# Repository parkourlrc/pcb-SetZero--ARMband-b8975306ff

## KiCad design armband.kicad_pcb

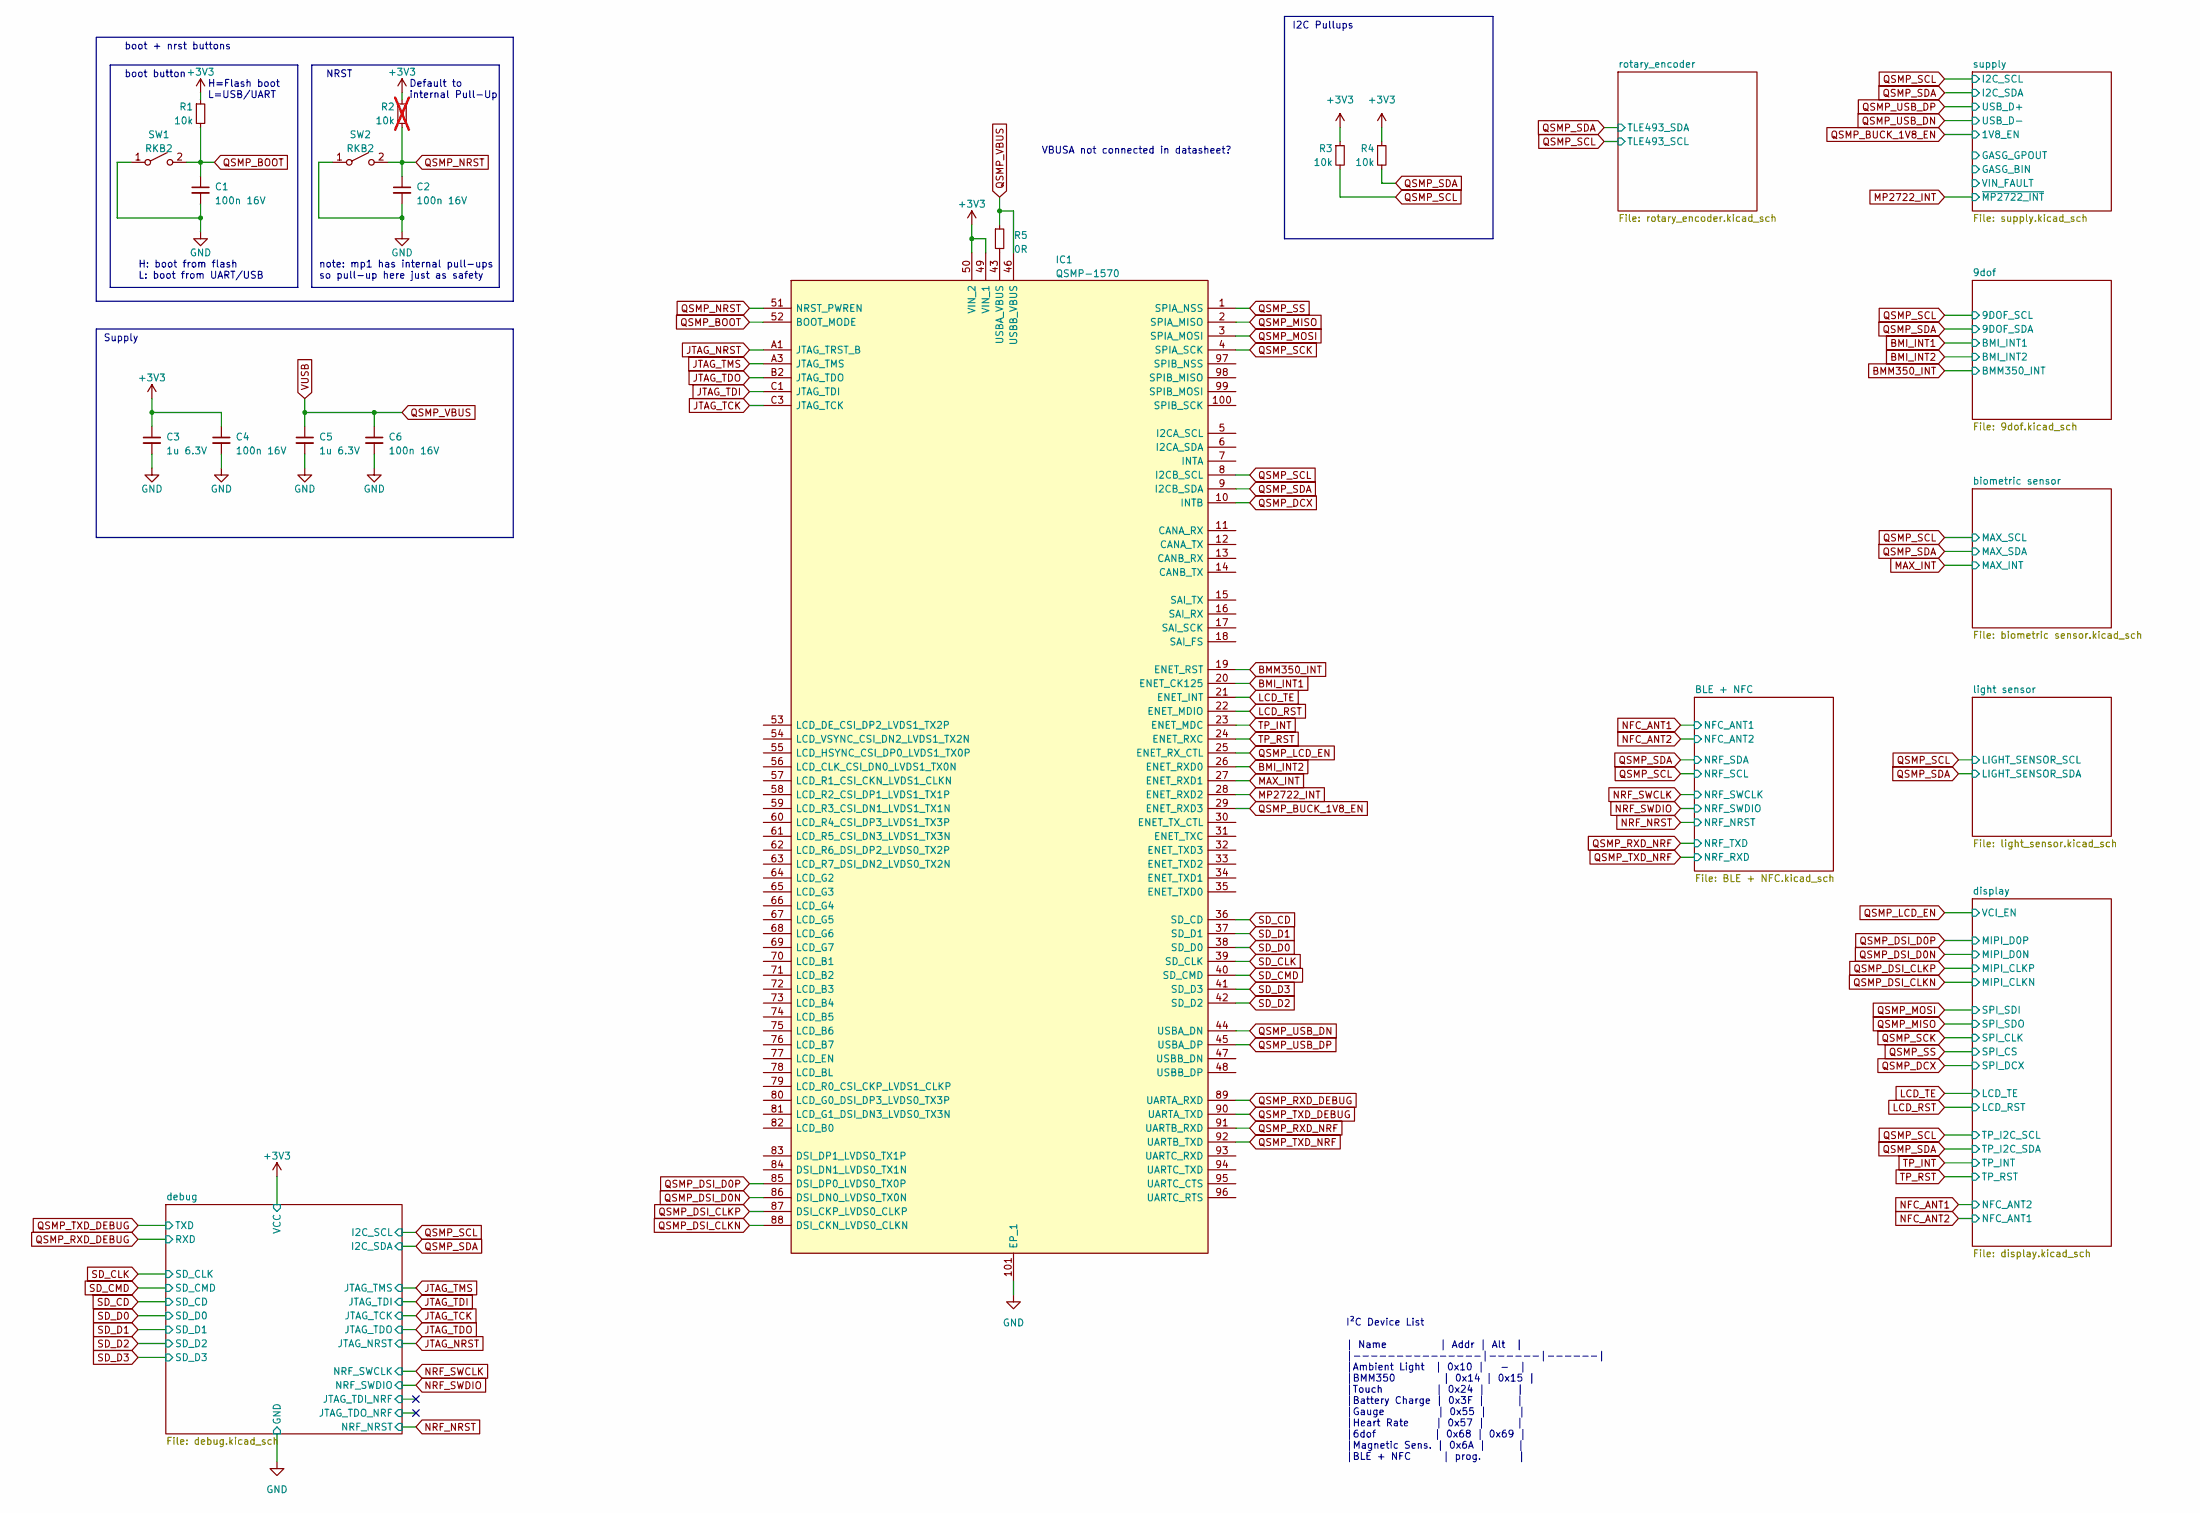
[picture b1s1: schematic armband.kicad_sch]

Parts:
C1, C2, C4, C6: 100n 16V; C_0402_1005Metric
C3, C5: 1u 6.3V; C_0201_0603Metric
IC1: QSMP-1570; QSMP1570_better; Mouser Part Number 951-QSMP-1570
R1: 10k; R_0201_0603Metric
R2: 10k; R_0201_0603Metric; not fitted
R3, R4: 10k; R_0603_1608Metric
R5: 0R; R_0201_0603Metric
SW1, SW2: RKB2

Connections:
+3V3: C3.1, C4.1, IC1.49 (VIN_1), IC1.50 (VIN_2), R1.1, R2.1, R3.1, R4.1; also elsewhere on the board
BMI_INT1: IC1.20 (ENET_CK125); also elsewhere on the board
BMI_INT2: IC1.26 (ENET_RXD0); also elsewhere on the board
BMM350_INT: IC1.19 (ENET_RST); also elsewhere on the board
GND: C1.2, C2.2, C3.2, C4.2, C5.2, C6.2, IC1.101 (EP_1), SW1.1 (A), SW2.1 (A); also elsewhere on the board
JTAG_NRST: IC1.A1 (JTAG_TRST_B); also elsewhere on the board
JTAG_TCK: IC1.C3 (JTAG_TCK); also elsewhere on the board
JTAG_TDI: IC1.C1 (JTAG_TDI); also elsewhere on the board
JTAG_TDO: IC1.B2 (JTAG_TDO); also elsewhere on the board
JTAG_TMS: IC1.A3 (JTAG_TMS); also elsewhere on the board
LCD_RST: IC1.22 (ENET_MDIO); also elsewhere on the board
LCD_TE: IC1.21 (ENET_INT); also elsewhere on the board
MAX_INT: IC1.27 (ENET_RXD1); also elsewhere on the board
MP2722_INT: IC1.28 (ENET_RXD2); also elsewhere on the board
unnamed: IC1.43 (USBA_VBUS), R5.2
QSMP_BOOT: C1.1, IC1.52 (BOOT_MODE), R1.2, SW1.2 (B)
QSMP_BUCK_1V8_EN: IC1.29 (ENET_RXD3); also elsewhere on the board
QSMP_DCX: IC1.10 (INTB); also elsewhere on the board
QSMP_DSI_CLKN: IC1.88 (DSI_CKN_LVDS0_CLKN); also elsewhere on the board
QSMP_DSI_CLKP: IC1.87 (DSI_CKP_LVDS0_CLKP); also elsewhere on the board
QSMP_DSI_D0N: IC1.86 (DSI_DN0_LVDS0_TX0N); also elsewhere on the board
QSMP_DSI_D0P: IC1.85 (DSI_DP0_LVDS0_TX0P); also elsewhere on the board
QSMP_LCD_EN: IC1.25 (ENET_RX_CTL); also elsewhere on the board
QSMP_MISO: IC1.2 (SPIA_MISO); also elsewhere on the board
QSMP_MOSI: IC1.3 (SPIA_MOSI); also elsewhere on the board
QSMP_NRST: C2.1, IC1.51 (NRST_PWREN), R2.2, SW2.2 (B)
QSMP_RXD_DEBUG: IC1.89 (UARTA_RXD); also elsewhere on the board
QSMP_RXD_NRF: IC1.91 (UARTB_RXD); also elsewhere on the board
QSMP_SCK: IC1.4 (SPIA_SCK); also elsewhere on the board
QSMP_SCL: IC1.8 (I2CB_SCL), R3.2; also elsewhere on the board
QSMP_SDA: IC1.9 (I2CB_SDA), R4.2; also elsewhere on the board
QSMP_SS: IC1.1 (SPIA_NSS); also elsewhere on the board
QSMP_TXD_DEBUG: IC1.90 (UARTA_TXD); also elsewhere on the board
QSMP_TXD_NRF: IC1.92 (UARTB_TXD); also elsewhere on the board
QSMP_USB_DN: IC1.44 (USBA_DN); also elsewhere on the board
QSMP_USB_DP: IC1.45 (USBA_DP); also elsewhere on the board
QSMP_VBUS: C5.1, C6.1, IC1.46 (USBB_VBUS), R5.1; also elsewhere on the board
SD_CD: IC1.36 (SD_CD); also elsewhere on the board
SD_CLK: IC1.39 (SD_CLK); also elsewhere on the board
SD_CMD: IC1.40 (SD_CMD); also elsewhere on the board
SD_D0: IC1.38 (SD_D0); also elsewhere on the board
SD_D1: IC1.37 (SD_D1); also elsewhere on the board
SD_D2: IC1.42 (SD_D2); also elsewhere on the board
SD_D3: IC1.41 (SD_D3); also elsewhere on the board
TP_INT: IC1.23 (ENET_MDC); also elsewhere on the board
TP_RST: IC1.24 (ENET_RXC); also elsewhere on the board

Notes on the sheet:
note: mp1 has internal pull-ups so pull-up here just as safety
boot + nrst buttons
NRST
H: boot from flash L: boot from UART/USB
boot button
I²C Device List | Name | Addr | Alt | |---------------|------|------| |Ambient Light | 0x10 | - | |BMM350 | 0x14 | 0x15 | |Touch | 0x24 | | |Battery Charge | 0x3F | | |Gauge | 0x55 | | |Heart Rate | 0x57 | | |6dof | 0x68 | 0x69 | |Magnetic Sens. | 0x6A | | |BLE + NFC | prog. |
VBUSA not connected in datasheet?
I2C Pullups
Default to internal Pull-Up
Supply
H=Flash boot L=USB/UART

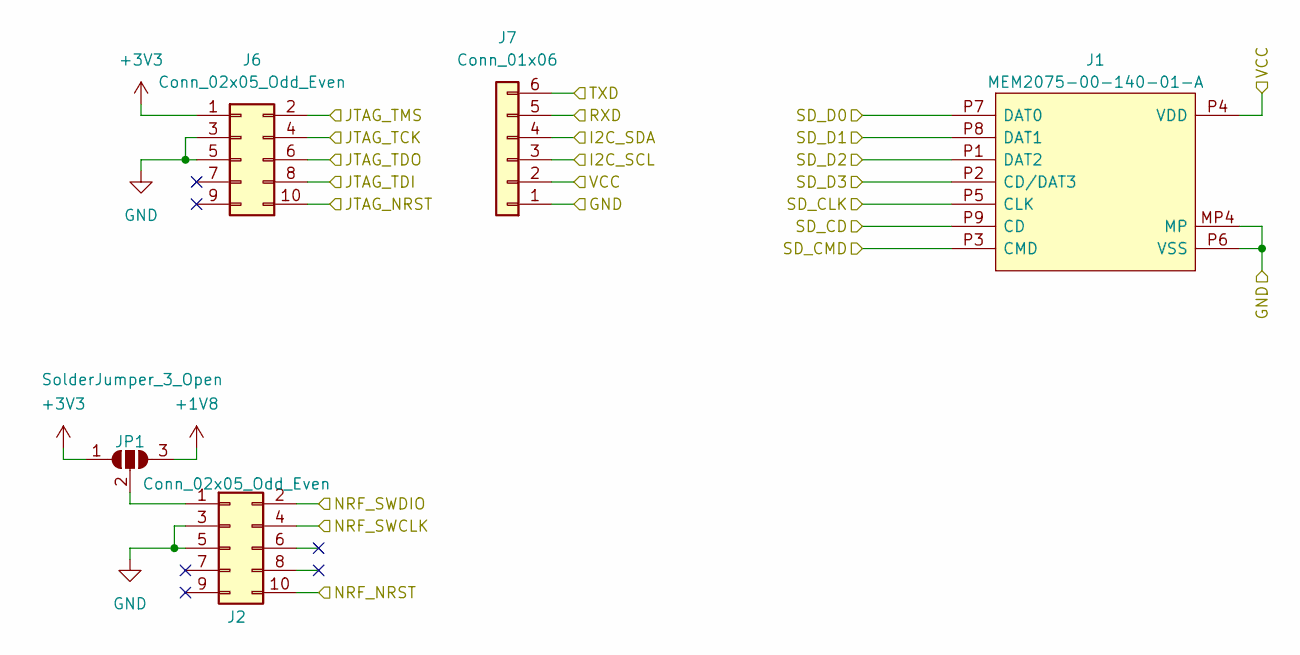
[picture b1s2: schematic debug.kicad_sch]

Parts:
J1: MEM2075-00-140-01-A; MEM20750014001A
J2, J6: Conn_02x05_Odd_Even; 2002112100010T4LF
J7: Conn_01x06; PinHeader_1x06_P2.54mm_Vertical
JP1: SolderJumper_3_Open; SolderJumper-3_P2.0mm_Open_TrianglePad1.0x1.5mm

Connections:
+1V8: JP1.3 (B); also elsewhere on the board
+3V3: J1.P4 (VDD), J6.1, J7.2, JP1.1 (A); also elsewhere on the board
GND: J1.MP1, J1.MP2, J1.MP3, J1.MP4 (MP), J1.P6 (VSS), J2.3, J2.5, J6.3, J6.5, J7.1; also elsewhere on the board
JTAG_NRST: J6.10; also elsewhere on the board
JTAG_TCK: J6.4; also elsewhere on the board
JTAG_TDI: J6.8; also elsewhere on the board
JTAG_TDO: J6.6; also elsewhere on the board
JTAG_TMS: J6.2; also elsewhere on the board
NRF_NRST: J2.10; also elsewhere on the board
NRF_SWCLK: J2.4; also elsewhere on the board
NRF_SWDIO: J2.2; also elsewhere on the board
unnamed: J2.1, JP1.2 (C)
QSMP_RXD_DEBUG: J7.5; also elsewhere on the board
QSMP_SCL: J7.3; also elsewhere on the board
QSMP_SDA: J7.4; also elsewhere on the board
QSMP_TXD_DEBUG: J7.6; also elsewhere on the board
SD_CD: J1.P9 (CD); also elsewhere on the board
SD_CLK: J1.P5 (CLK); also elsewhere on the board
SD_CMD: J1.P3 (CMD); also elsewhere on the board
SD_D0: J1.P7 (DAT0); also elsewhere on the board
SD_D1: J1.P8 (DAT1); also elsewhere on the board
SD_D2: J1.P1 (DAT2); also elsewhere on the board
SD_D3: J1.P2 (CD/DAT3); also elsewhere on the board

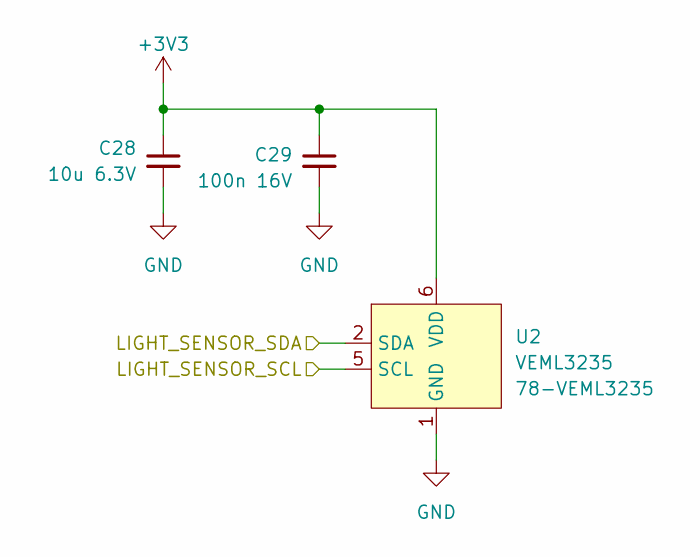
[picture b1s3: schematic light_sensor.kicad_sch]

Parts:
C28: 10u 6.3V; C_0402_1005Metric
C29: 100n 16V; C_0402_1005Metric
U2: VEML3235

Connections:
+3V3: C28.1, C29.1, U2.6 (VDD); also elsewhere on the board
GND: C28.2, C29.2, U2.1 (GND); also elsewhere on the board
QSMP_SCL: U2.5 (SCL); also elsewhere on the board
QSMP_SDA: U2.2 (SDA); also elsewhere on the board

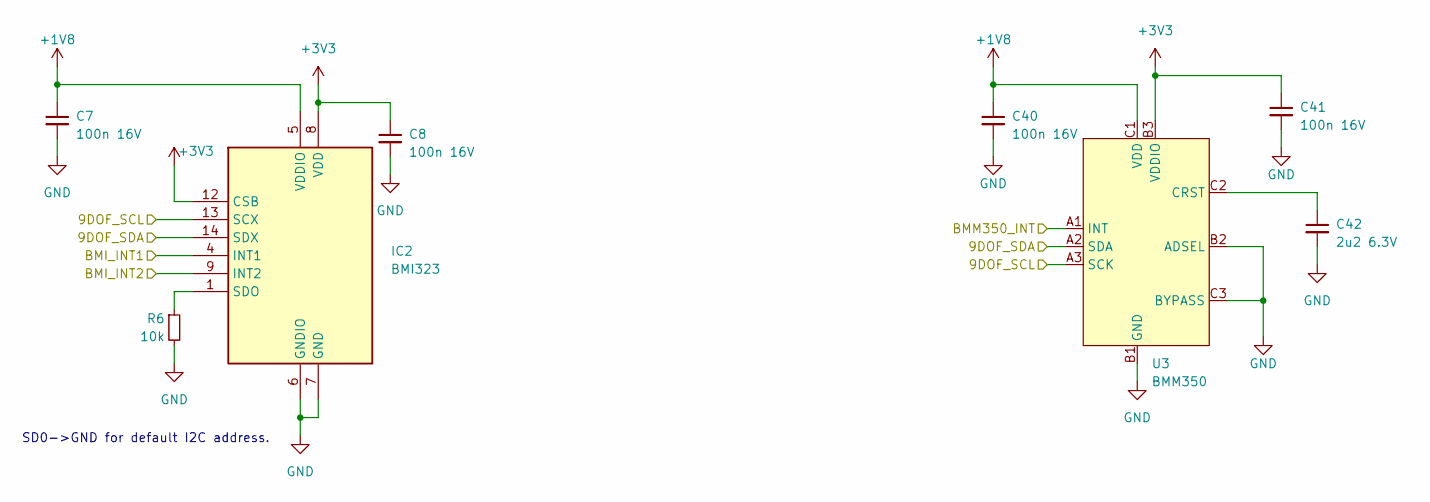
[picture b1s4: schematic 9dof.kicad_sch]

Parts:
C7, C8, C40, C41: 100n 16V; C_0402_1005Metric
C42: 2u2 6.3V; C_0201_0603Metric
IC2: BMI323; Mouser Part Number 262-BMI323
R6: 10k; R_0201_0603Metric
U3: BMM350; bmm350

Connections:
+1V8: C7.1, C40.1, IC2.5 (VDDIO), U3.C1 (VDD); also elsewhere on the board
+3V3: C8.1, C41.1, IC2.8 (VDD), IC2.12 (CSB), U3.B3 (VDDIO); also elsewhere on the board
BMI_INT1: IC2.4 (INT1); also elsewhere on the board
BMI_INT2: IC2.9 (INT2); also elsewhere on the board
BMM350_INT: U3.A1 (INT); also elsewhere on the board
GND: C7.2, C8.2, C40.2, C41.2, C42.2, IC2.6 (GNDIO), IC2.7 (GND), R6.2, U3.B1 (GND), U3.B2 (ADSEL), U3.C3 (BYPASS); also elsewhere on the board
unnamed: IC2.1 (SDO), R6.1
unnamed: C42.1, U3.C2 (CRST)
QSMP_SCL: IC2.13 (SCX), U3.A3 (SCK); also elsewhere on the board
QSMP_SDA: IC2.14 (SDX), U3.A2 (SDA); also elsewhere on the board

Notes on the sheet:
SD0->GND for default I2C address.

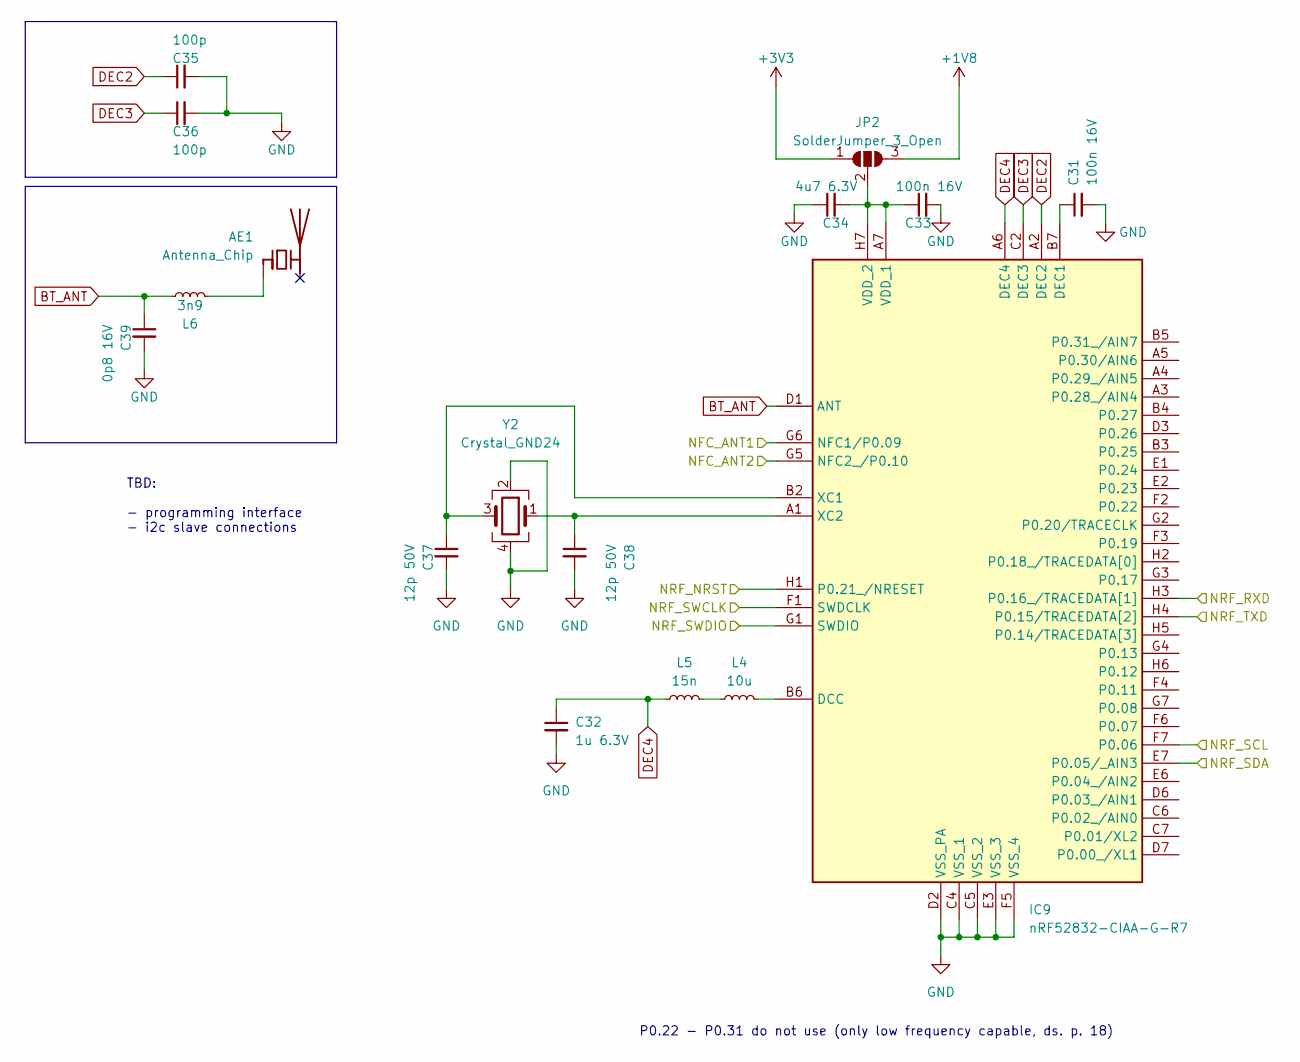
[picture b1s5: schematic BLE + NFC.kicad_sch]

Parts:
AE1: Antenna_Chip; ST0147-00-011-A
C31, C33: 100n 16V; C_0402_1005Metric
C32: 1u 6.3V; C_0201_0603Metric
C34: 4u7 6.3V; C_0402_1005Metric
C35, C36: 100p; C_0402_1005Metric
C37, C38: 12p 50V; C_0201_0603Metric
C39: 0p8 16V; C_0402_1005Metric
IC9: nRF52832-CIAA-G-R7; BGA50C40P7X8_296X323X40
JP2: SolderJumper_3_Open; SolderJumper-3_P1.3mm_Open_RoundedPad1.0x1.5mm
L4: 10u; L_0603_1608Metric
L5: 15n; L_0201_0603Metric
L6: 3n9; L_0402_1005Metric
Y2: Crystal_GND24; CX2016SA

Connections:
+1V8: JP2.3 (B); also elsewhere on the board
+3V3: JP2.1 (A); also elsewhere on the board
BT_ANT: C39.1, IC9.D1 (ANT), L6.2
DEC2: C35.1, IC9.A2 (DEC2)
DEC3: C36.1, IC9.C2 (DEC3)
DEC4: C32.1, IC9.A6 (DEC4), L5.1
GND: C31.2, C32.2, C33.2, C34.1, C35.2, C36.2, C37.2, C38.2, C39.2, IC9.C4 (VSS_1), IC9.C5 (VSS_2), IC9.D2 (VSS_PA), IC9.E3 (VSS_3), IC9.F5 (VSS_4), Y2.2, Y2.4; also elsewhere on the board
NFC_ANT1: IC9.G6 (NFC1/P0.09); also elsewhere on the board
NFC_ANT2: IC9.G5 (NFC2_/P0.10); also elsewhere on the board
NRF_NRST: IC9.H1 (P0.21_/NRESET); also elsewhere on the board
NRF_SWCLK: IC9.F1 (SWDCLK); also elsewhere on the board
NRF_SWDIO: IC9.G1 (SWDIO); also elsewhere on the board
unnamed: AE1.1 (FEED), L6.1
unnamed: IC9.B6 (DCC), L4.2
unnamed: C31.1, IC9.B7 (DEC1)
unnamed: C33.1, C34.2, IC9.A7 (VDD_1), IC9.H7 (VDD_2), JP2.2 (C)
unnamed: C37.1, IC9.B2 (XC1), Y2.3
unnamed: C38.1, IC9.A1 (XC2), Y2.1
unnamed: L4.1, L5.2
QSMP_RXD_NRF: IC9.H4 (P0.15/TRACEDATA[2]); also elsewhere on the board
QSMP_SCL: IC9.F7 (P0.06); also elsewhere on the board
QSMP_SDA: IC9.E7 (P0.05/_AIN3); also elsewhere on the board
QSMP_TXD_NRF: IC9.H3 (P0.16_/TRACEDATA[1]); also elsewhere on the board

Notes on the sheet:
P0.22 - P0.31 do not use (only low frequency capable, ds. p. 18)
TBD: - programming interface - i2c slave connections

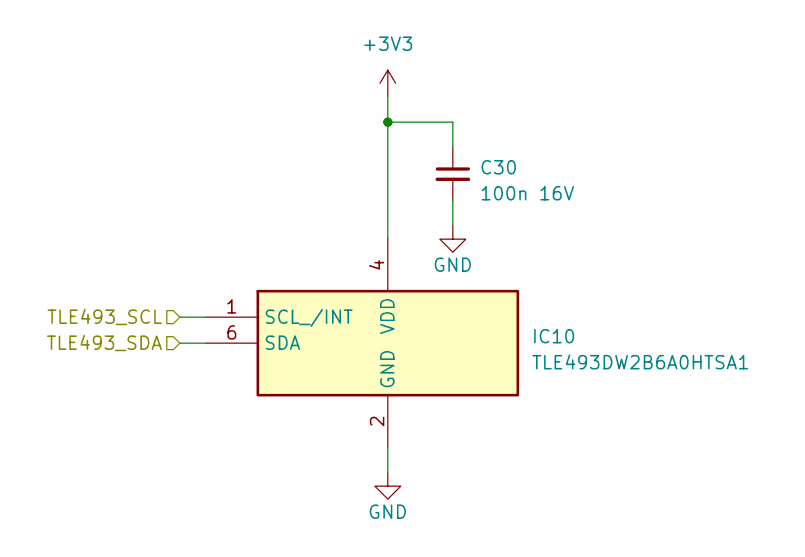
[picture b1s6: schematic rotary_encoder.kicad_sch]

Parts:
C30: 100n 16V; C_0402_1005Metric
IC10: TLE493DW2B6A0HTSA1; SOT95P280X110-6N; Mouser Part Number 726-TLE493DW2B6A0HTS

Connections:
+3V3: C30.1, IC10.4 (VDD); also elsewhere on the board
GND: C30.2, IC10.2 (GND), IC10.3 (GND_2), IC10.5 (GND_3); also elsewhere on the board
QSMP_SCL: IC10.1 (SCL_/INT); also elsewhere on the board
QSMP_SDA: IC10.6 (SDA); also elsewhere on the board

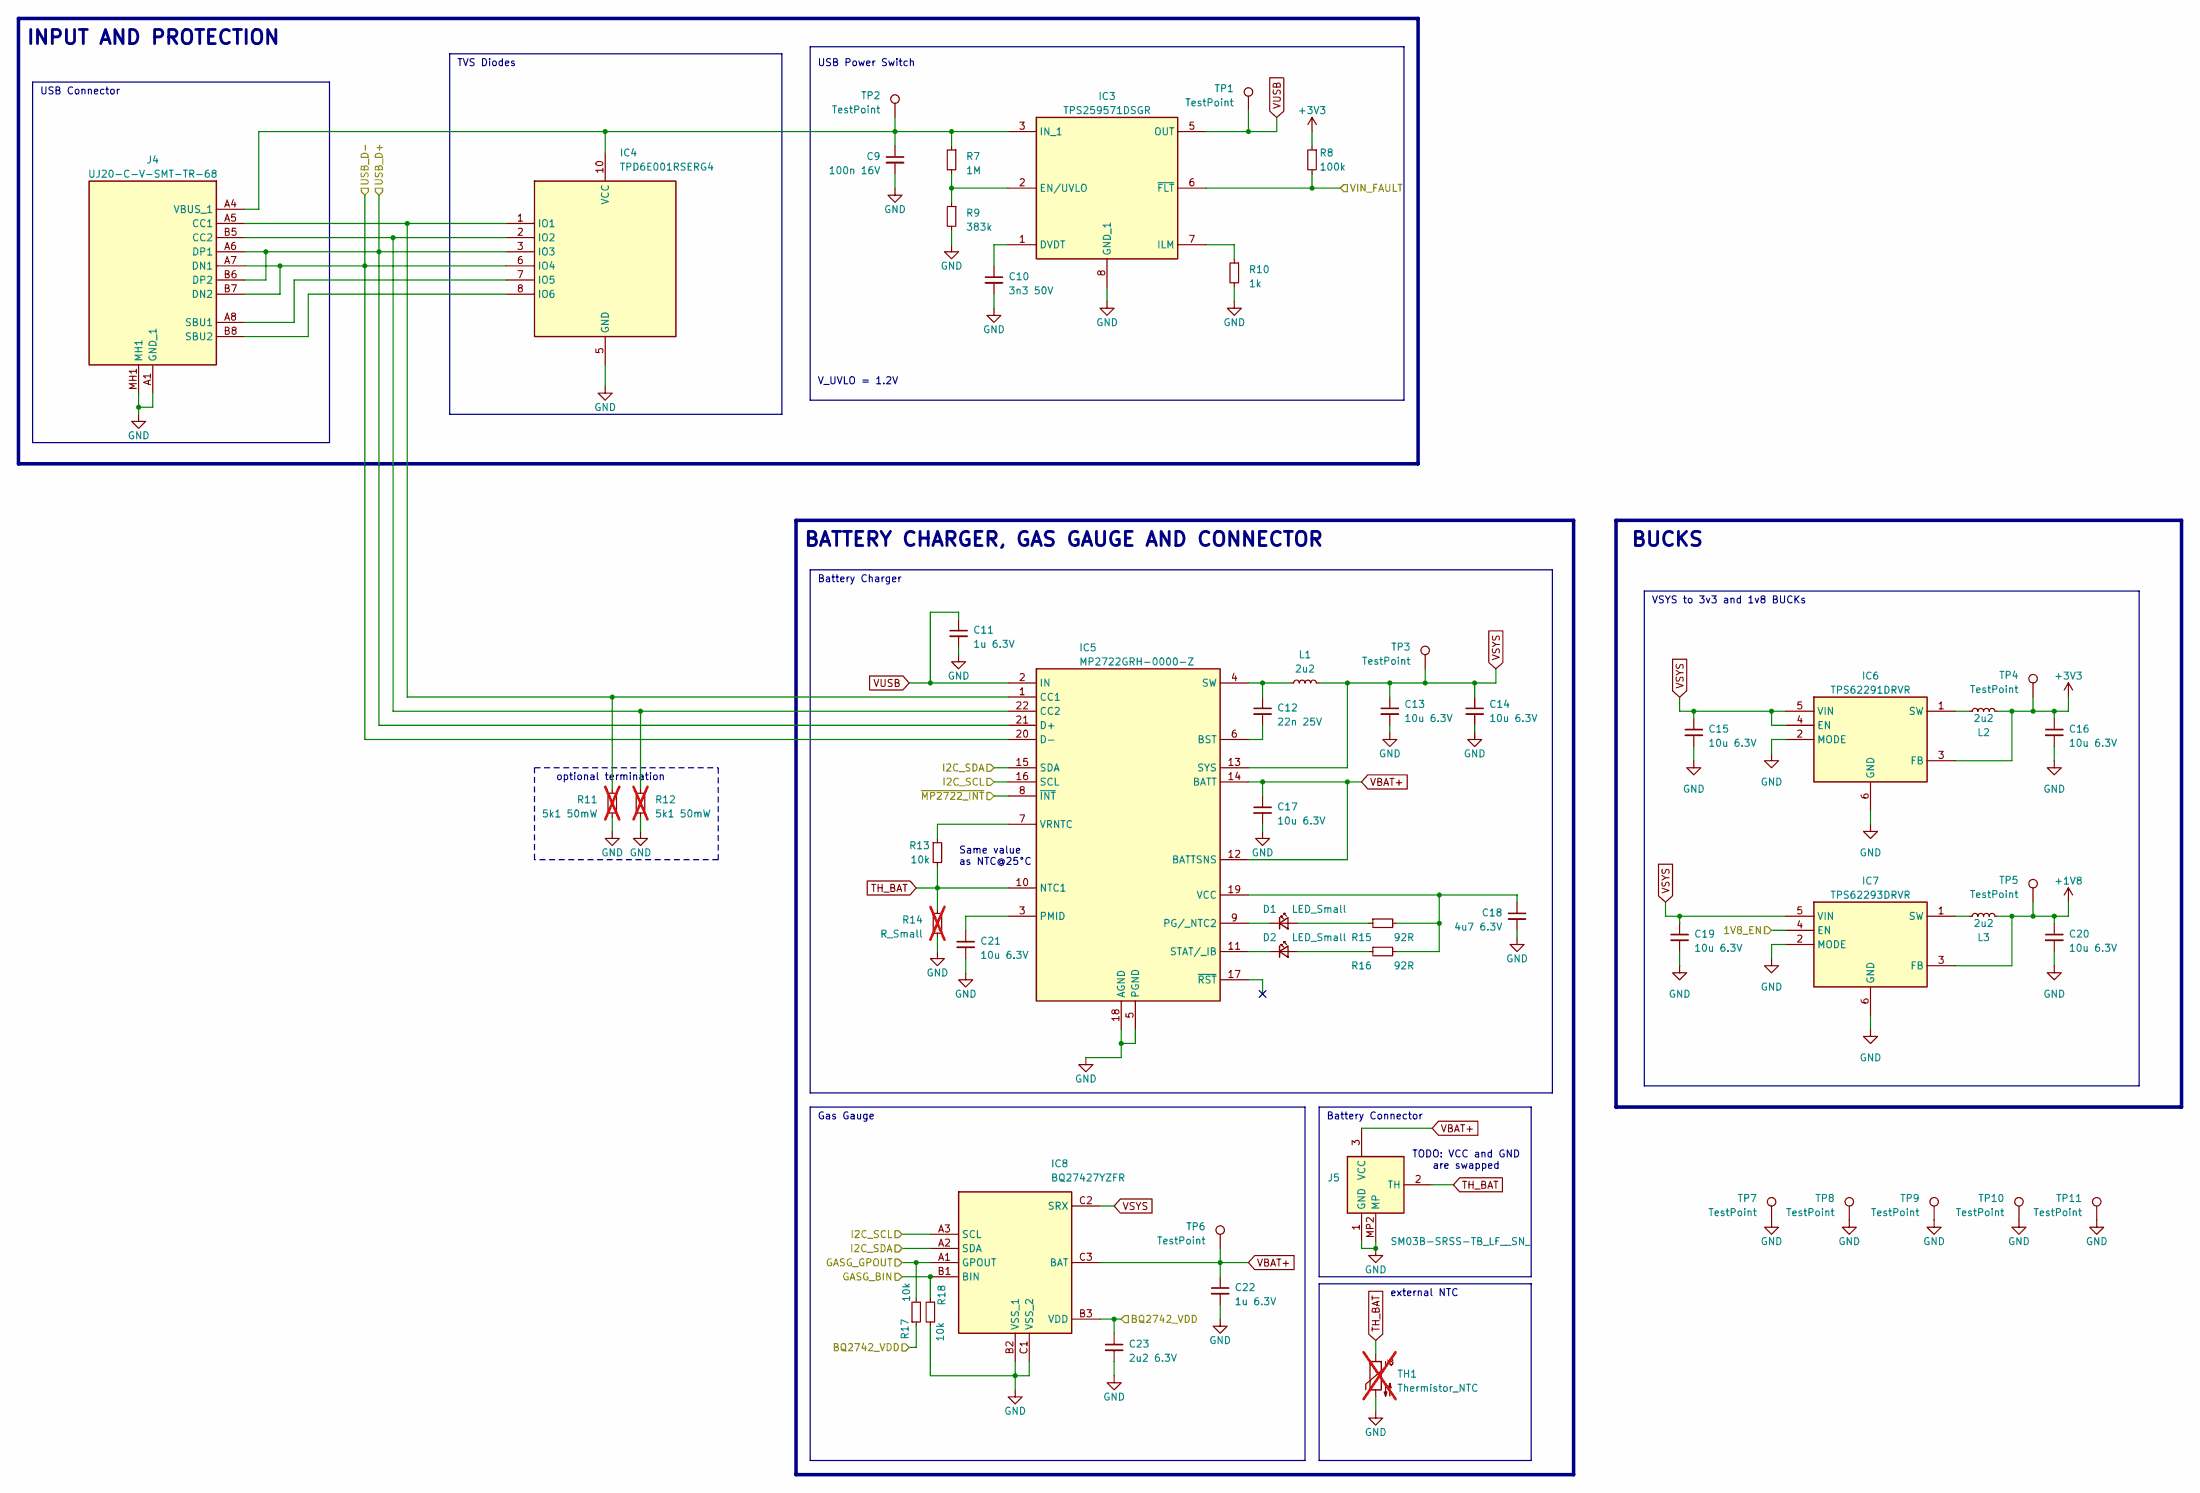
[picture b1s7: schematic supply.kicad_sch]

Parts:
C9: 100n 16V; C_0402_1005Metric
C10: 3n3 50V; C_0402_1005Metric
C11, C22: 1u 6.3V; C_0201_0603Metric
C12: 22n 25V; C_0402_1005Metric
C13, C14, C15, C16, C17, C19, C20, C21: 10u 6.3V; C_0402_1005Metric
C18: 4u7 6.3V; C_0402_1005Metric
C23: 2u2 6.3V; C_0201_0603Metric
D1, D2: LED_Small; LEDC1608X80N
IC3: TPS259571DSGR; SON50P200X200X80-9N
IC4: TPD6E001RSERG4; Mouser Part Number 595-TPD6E001RSERG4
IC5: MP2722GRH-0000-Z; MP2722GRH0000Z
IC6: TPS62291DRVR; SON65P200X200X80-7N
IC7: TPS62293DRVR; SON65P200X200X80-7N
IC8: BQ27427YZFR; BGA9C50P3X3_158X162X62
J4: UJ20-C-V-SMT-TR-68; UJ20CVSMTTR68; Mouser Part Number 179-UJ20-C-V-SMTTR68
J5: SM03B-SRSS-TB_LF__SN_; SM03BSRSSTBLFSN; Manufacturer_Part_Number SM03B-SRSS-TB(LF)(SN)
L1: 2u2; INDC3225X120N
L2, L3: 2u2; LQM2MPN1R0NG0L
R7: 1M; R_0201_0603Metric
R8: 100k; R_0201_0603Metric
R9: 383k; R_0201_0603Metric
R10: 1k; R_0201_0603Metric
R11, R12: 5k1 50mW; R_0201_0603Metric; not fitted
R13, R17, R18: 10k; R_0201_0603Metric
R14: R_Small; R_0201_0603Metric; not fitted
R15, R16: 92R; R_0201_0603Metric
TH1: Thermistor_NTC; CTTS-203856-S02; not fitted
TP1, TP2, TP3, TP4, TP5, TP6, TP7, TP8, TP9, TP10, TP11: TestPoint; TestPoint_Pad_D1.0mm

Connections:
+1V8: C20.1, IC7.3 (FB), L3.1, TP5.1; also elsewhere on the board
+3V3: C16.1, IC6.3 (FB), L2.1, R8.1, TP4.1; also elsewhere on the board
/supply/BQ2742_VDD: C23.1, IC8.B3 (VDD), R17.1
/supply/GASG_BIN: IC8.B1 (BIN), R18.1
/supply/GASG_GPOUT: IC8.A1 (GPOUT), R17.2
/supply/VIN_FAULT: IC3.6 (~FLT), R8.2
GND: C9.2, C10.2, C11.2, C13.2, C14.2, C15.2, C16.2, C17.2, C18.2, C19.2, C20.2, C21.2, C22.2, C23.2, IC3.8 (GND_1), IC3.9 (GND_2), IC4.5 (GND), IC5.5 (PGND), IC5.18 (AGND), IC6.2 (MODE), IC6.6 (GND), IC6.7 (EP), IC7.2 (MODE), IC7.6 (GND), IC7.7 (EP), IC8.B2 (VSS_1), IC8.C1 (VSS_2), J4.A1 (GND_1), J4.A12 (GND_2), J4.B1 (GND_3), J4.B12 (GND_4), J4.MH1, J4.MH2, J4.MH3, J4.MH4, J5.1 (GND), J5.MP1 (MP), J5.MP2 (MP), R9.2, R10.2, R11.2, R12.2, R14.2, R18.2, TH1.2, TP7.1, TP8.1, TP9.1, TP10.1, TP11.1; also elsewhere on the board
MP2722_INT: IC5.8 (~INT); also elsewhere on the board
unnamed: D1.2 (A), R15.1
unnamed: D1.1 (K), IC5.9 (PG/_NTC2)
unnamed: D2.2 (A), R16.1
unnamed: D2.1 (K), IC5.11 (STAT/_IB)
unnamed: C10.1, IC3.1 (DVDT)
unnamed: IC3.2 (EN/UVLO), R7.2, R9.1
unnamed: IC3.7 (ILM), R10.1
unnamed: C9.1, IC3.3 (IN_1), IC3.4 (IN_2), IC4.10 (VCC), J4.A4 (VBUS_1), J4.A9 (VBUS_2), J4.B4 (VBUS_3), J4.B9 (VBUS_4), R7.1, TP2.1
unnamed: IC4.1 (IO1), IC5.1 (CC1), J4.A5 (CC1), R11.1
unnamed: IC4.2 (IO2), IC5.22 (CC2), J4.B5 (CC2), R12.1
unnamed: IC4.7 (IO5), J4.A8 (SBU1)
unnamed: IC4.8 (IO6), J4.B8 (SBU2)
unnamed: C12.2, IC5.6 (BST)
unnamed: C21.1, IC5.3 (PMID)
unnamed: C12.1, IC5.4 (SW), L1.1
unnamed: C18.1, IC5.19 (VCC), R15.2, R16.2
unnamed: IC5.7 (VRNTC), R13.1
unnamed: IC6.1 (SW), L2.2
unnamed: IC7.1 (SW), L3.2
QSMP_BUCK_1V8_EN: IC7.4 (EN); also elsewhere on the board
QSMP_SCL: IC5.16 (SCL), IC8.A3 (SCL); also elsewhere on the board
QSMP_SDA: IC5.15 (SDA), IC8.A2 (SDA); also elsewhere on the board
QSMP_USB_DN: IC4.6 (IO4), IC5.20 (D-), J4.A7 (DN1), J4.B7 (DN2); also elsewhere on the board
QSMP_USB_DP: IC4.3 (IO3), IC5.21 (D+), J4.A6 (DP1), J4.B6 (DP2); also elsewhere on the board
QSMP_VBUS: C11.1, IC3.5 (OUT), IC5.2 (IN), TP1.1; also elsewhere on the board
TH_BAT: IC5.10 (NTC1), J5.2 (TH), R13.2, R14.1, TH1.1
VBAT+: C17.1, C22.1, IC5.12 (BATTSNS), IC5.14 (BATT), IC8.C3 (BAT), J5.3 (VCC), TP6.1
VSYS: C13.1, C14.1, C15.1, C19.1, IC5.13 (SYS), IC6.4 (EN), IC6.5 (VIN), IC7.5 (VIN), IC8.C2 (SRX), L1.2, TP3.1

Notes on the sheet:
Same value as NTC@25°C
TODO: VCC and GND are swapped
BUCKS
optional termination
V_UVLO = 1.2V
Battery Connector
USB Power Switch
Gas Gauge
TVS Diodes
INPUT AND PROTECTION
VSYS to 3v3 and 1v8 BUCKs
external NTC
BATTERY CHARGER, GAS GAUGE AND CONNECTOR
USB Connector
Battery Charger

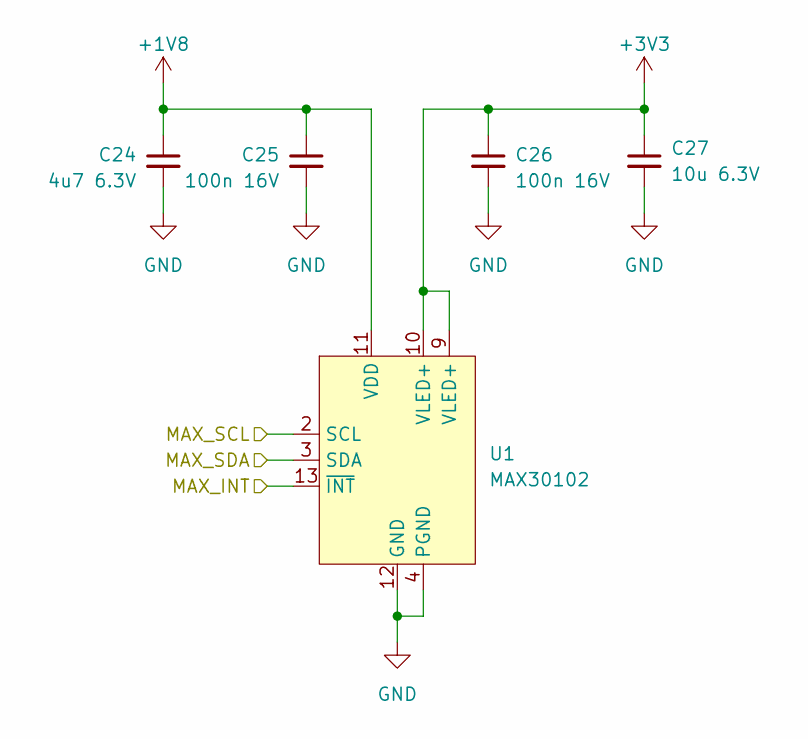
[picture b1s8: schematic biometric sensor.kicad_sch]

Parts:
C24: 4u7 6.3V; C_0402_1005Metric
C25, C26: 100n 16V; C_0402_1005Metric
C27: 10u 6.3V; C_0402_1005Metric
U1: MAX30102

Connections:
+1V8: C24.1, C25.1, U1.11 (VDD); also elsewhere on the board
+3V3: C26.1, C27.1, U1.9 (VLED+), U1.10 (VLED+); also elsewhere on the board
GND: C24.2, C25.2, C26.2, C27.2, U1.4 (PGND), U1.12 (GND); also elsewhere on the board
MAX_INT: U1.13 (~INT); also elsewhere on the board
QSMP_SCL: U1.2 (SCL); also elsewhere on the board
QSMP_SDA: U1.3 (SDA); also elsewhere on the board

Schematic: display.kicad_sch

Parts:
J3: AXF5D3012; display_AXF5D3012

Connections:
+1V8: J3.13 (VIO18), J3.14 (VIO18); also elsewhere on the board
+3V3: J3.8 (TP_VDD), J3.31 (VPH_PWR); also elsewhere on the board
GND: J3.2 (GND), J3.9 (GND), J3.12 (GND), J3.18 (GND), J3.24 (GND), J3.27 (GND), J3.30 (GND), J3.33 (GND), J3.34 (GND); also elsewhere on the board
LCD_RST: J3.10 (LCD_RST); also elsewhere on the board
LCD_TE: J3.11 (LCD_TE); also elsewhere on the board
NFC_ANT1: J3.16 (NFC_ANT2); also elsewhere on the board
NFC_ANT2: J3.17 (NFC_ANT1); also elsewhere on the board
unnamed: J3.5 (NC), J3.15 (NC)
QSMP_DCX: J3.21 (SPI_DCX); also elsewhere on the board
QSMP_DSI_CLKN: J3.26 (MIPI_CLKN); also elsewhere on the board
QSMP_DSI_CLKP: J3.25 (MIPI_CLKP); also elsewhere on the board
QSMP_DSI_D0N: J3.29 (MIPI_DON); also elsewhere on the board
QSMP_DSI_D0P: J3.28 (MIPI_DOP); also elsewhere on the board
QSMP_LCD_EN: J3.1 (VCI_EN); also elsewhere on the board
QSMP_MISO: J3.19 (SPI_SDO); also elsewhere on the board
QSMP_MOSI: J3.20 (SPI_SDI); also elsewhere on the board
QSMP_SCK: J3.22 (SPI_CLK); also elsewhere on the board
QSMP_SCL: J3.4 (TP_12C_SCL); also elsewhere on the board
QSMP_SDA: J3.3 (TP_12C_SDA); also elsewhere on the board
QSMP_SS: J3.23 (SPI_CS); also elsewhere on the board
TP_INT: J3.7 (TP_INT); also elsewhere on the board
TP_RST: J3.6 (TP_RST); also elsewhere on the board

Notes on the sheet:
TODO: footprint überprüfen - nummerierung pins! - pins 31, 32, 33, 34 richtig? - MP5-8 gnd? IMPORTANT: - version UH hat größere power pins und ist kleiner -> das ist der den wir auch verwenden wollen/müssen da er auf dem display verbaut ist -> mouser hat UH aktuell nicht lagernd

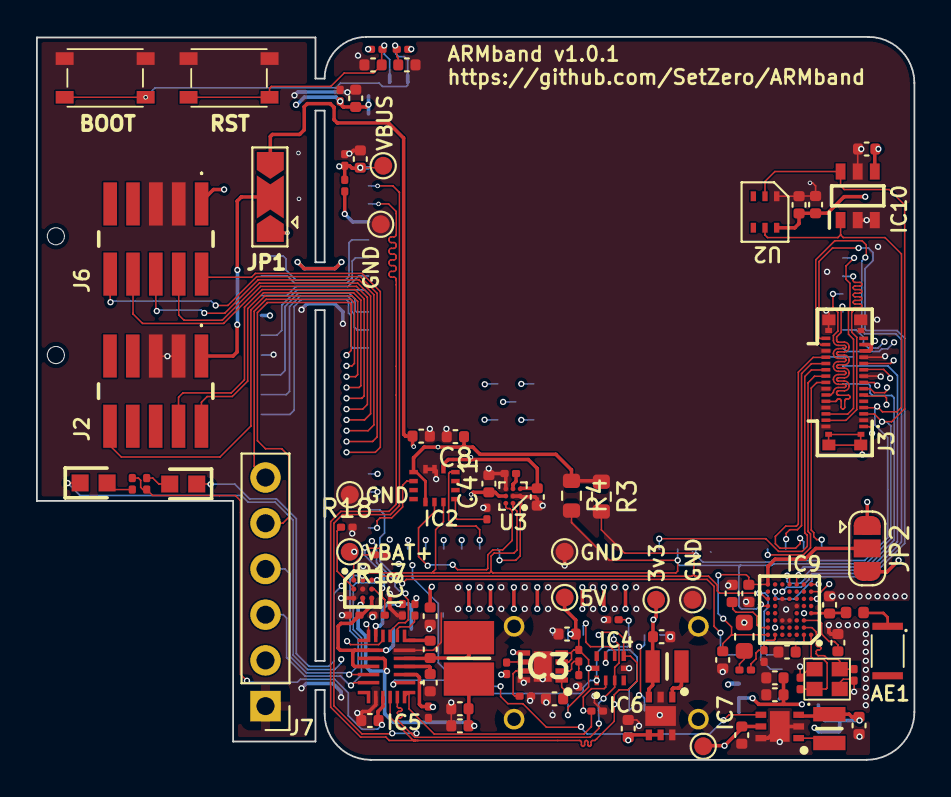
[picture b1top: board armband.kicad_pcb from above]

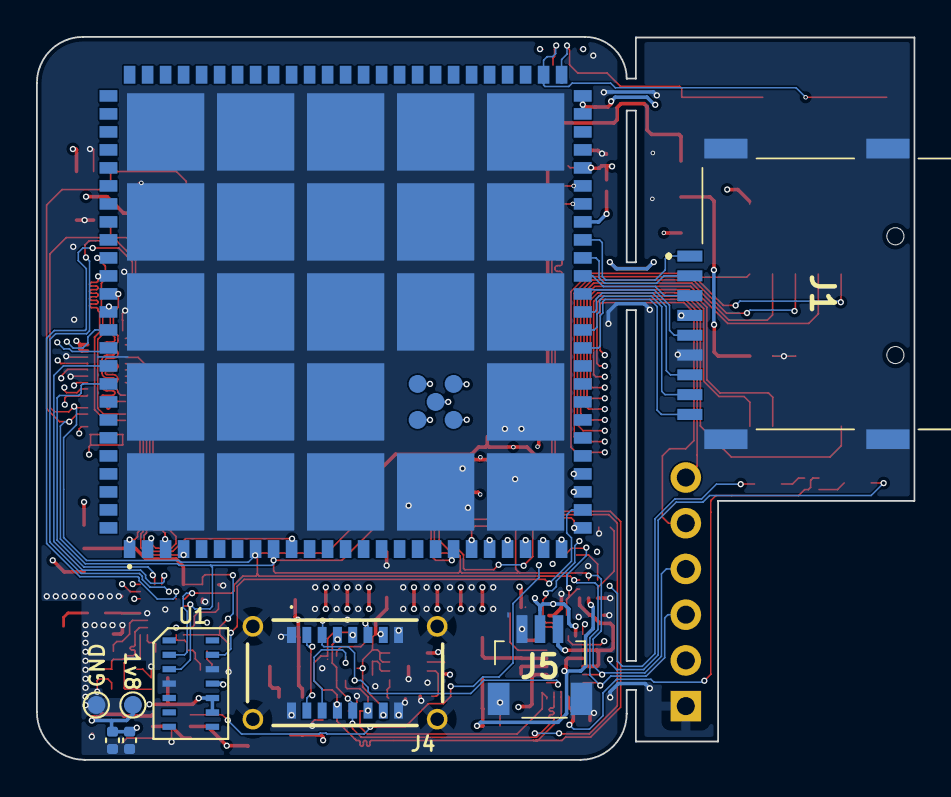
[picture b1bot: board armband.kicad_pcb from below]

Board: 6 copper layers, 48.8 x 40.2 mm, 105 parts (9 on the bottom side), 93 nets.

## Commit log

2024-05-30 Fix Errors from Version 1
    - fix light sensor pin mixup
    - fix gas gauge floating pin
    - fix battery connector mirrored pinout
    - switch usb on STM32MP1
2024-05-30 Fix light sensor sda/scl
2024-06-08 Update VDDIO of 9dof
2024-06-08 progressed routing
2024-06-15 added new buttons + changed i2c pullups
